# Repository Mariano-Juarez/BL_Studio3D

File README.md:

# BL_Studio3D
ALIK (Alindado,Juarez,Luna,Barrientos)

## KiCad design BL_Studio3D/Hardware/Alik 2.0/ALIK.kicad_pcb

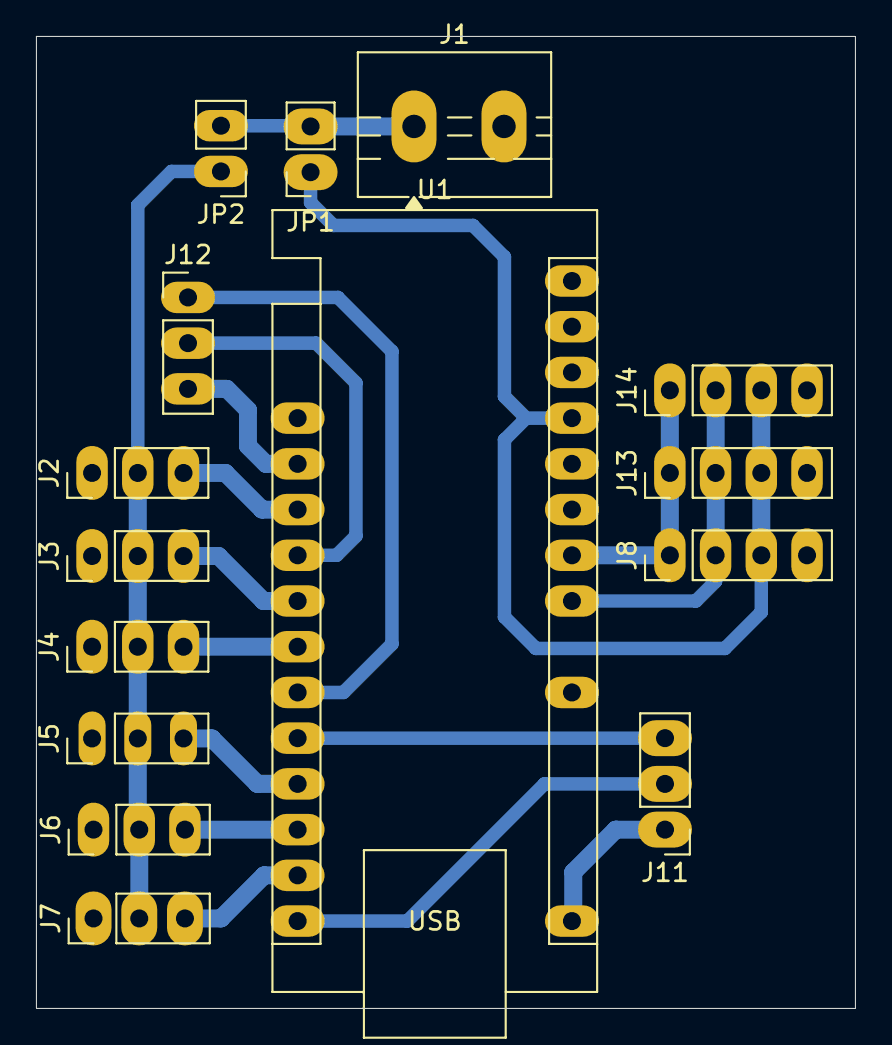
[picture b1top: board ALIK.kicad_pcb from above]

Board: 2 copper layers, 45.5 x 54.0 mm, 15 parts (0 on the bottom side), 17 nets.

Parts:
J1: Screw_Terminal_01x02; TerminalBlock_MaiXu_MX126-5.0-02P_1x02_P5.00mm
J2, J3, J4, J5, J6, J7, J11, J12: Conn_01x03_Pin; PinHeader_1x03_P2.54mm_Vertical
J8, J13, J14: Conn_01x04_Pin; PinHeader_1x04_P2.54mm_Vertical
JP1: Jumper_2_Open; PinSocket_1x02_P2.54mm_Vertical
JP2: Jumper_2_Open; PinHeader_1x02_P2.54mm_Vertical
U1: ARDUINO_NANO_A000005; Arduino_Nano

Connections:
+5V: J1.1, J8.3, J13.3, J14.3, JP1.1 (A), JP1.2 (B), JP2.2 (B), U1.27 (5V)
/D2: J12.3, U1.5 (D2)
/D3: J2.3, U1.6 (D3)
/D4: J12.2, U1.7 (D4)
/D5: J3.3, U1.8 (D5)
/D6: J4.3, U1.9 (D6)
/D7: J12.1, U1.10 (D7)
/D8: J11.3, U1.11 (D8)
/D9: J5.3, U1.12 (D9)
/D10: J6.3, U1.13 (D10)
/D11: J7.3, U1.14 (D11)
/D12: J11.2, U1.15 (D12)
/D13: J11.1, U1.16 (D13)
/SCL: J8.1, J13.1, J14.1, U1.24 (A5)
/SDA: J8.2, J14.2, U1.23 (A4)
/VCC: J2.2, J3.2, J4.2, J5.2, J6.2, J7.2, JP2.1 (A)
GND: J1.2, J2.1, J3.1, J4.1, J5.1, J6.1, J7.1, J8.4, J13.4, J14.4, U1.29 (GND_2)

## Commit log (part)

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2026-06-17 1er Commit
2026-06-17 2do Commit
2026-06-26 3er commit
